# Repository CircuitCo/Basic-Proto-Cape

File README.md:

Basic-Proto-Cape
================
The Basic Proto Cape is designed to break out 26 signals from the expansion headers of the BeagleBone Black including GPIO, I2C, SPI, UART, PWM, analog inputs, +5V, +3V3, and +1.8V (analog). These signals can be accessed via a 26-pin male header.

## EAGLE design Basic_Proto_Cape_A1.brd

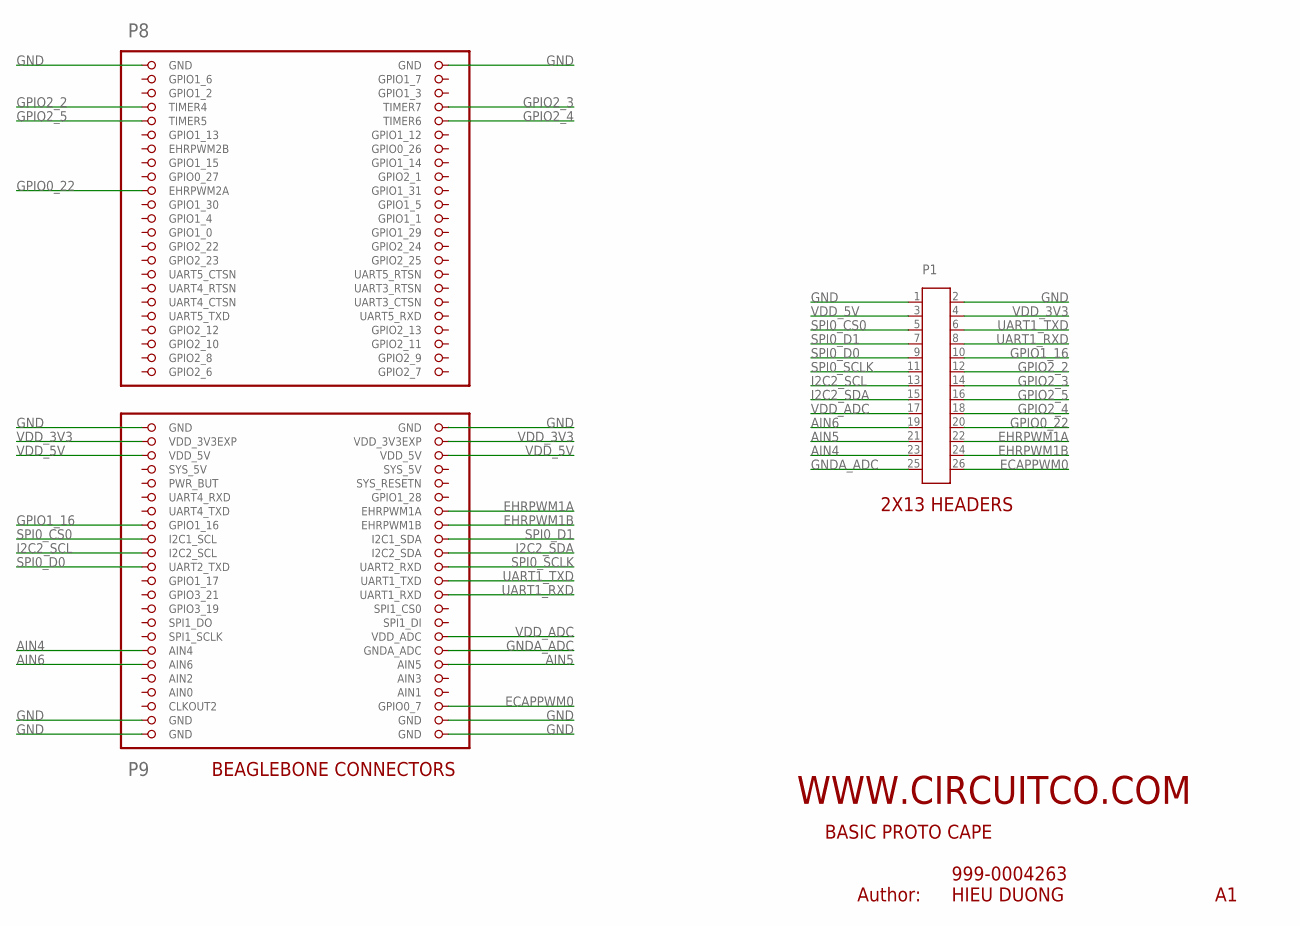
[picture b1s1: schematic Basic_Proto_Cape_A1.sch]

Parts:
P1: HEADER2X13TH; 2X13-TH
U1: BB_OL_GENPROTO

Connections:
AIN0: U1.85 (AIN0)
AIN4: P1.23, U1.79 (AIN4)
AIN5: P1.21, U1.82 (AIN5)
AIN6: P1.19, U1.81 (AIN6)
ECAPPWM0: P1.26, U1.88 (GPIO0_7)
EHRPWM1A: P1.22, U1.60 (EHRPWM1A)
EHRPWM1B: P1.24, U1.62 (EHRPWM1B)
GND: P1.1, P1.2, U1.1 (GND), U1.2 (GND), U1.47 (GND), U1.48 (GND), U1.89 (GND), U1.90 (GND), U1.91 (GND), U1.92 (GND)
GNDA_ADC: P1.25, U1.80 (GNDA_ADC)
GPIO0_22: P1.20, U1.19 (EHRPWM2A)
GPIO1_16: P1.10, U1.61 (GPIO1_16)
GPIO2_2: P1.12, U1.7 (TIMER4)
GPIO2_3: P1.14, U1.8 (TIMER7)
GPIO2_4: P1.18, U1.10 (TIMER6)
GPIO2_5: P1.16, U1.9 (TIMER5)
I2C2_SCL: P1.13, U1.65 (I2C2_SCL)
I2C2_SDA: P1.15, U1.66 (I2C2_SDA)
SPI0_CS0: P1.5, U1.63 (I2C1_SCL)
SPI0_D0: P1.9, U1.67 (UART2_TXD)
SPI0_D1: P1.7, U1.64 (I2C1_SDA)
SPI0_SCLK: P1.11, U1.68 (UART2_RXD)
SYS_5V: U1.53 (SYS_5V)
UART1_RXD: P1.8, U1.72 (UART1_RXD)
UART1_TXD: P1.6, U1.70 (UART1_TXD)
VDD_3V3: P1.4, U1.49 (VDD_3V3EXP), U1.50 (VDD_3V3EXP)
VDD_5V: P1.3, U1.51 (VDD_5V), U1.52 (VDD_5V)
VDD_ADC: P1.17, U1.78 (VDD_ADC)

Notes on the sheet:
BEAGLEBONE CONNECTORS
2X13 HEADERS
Author:

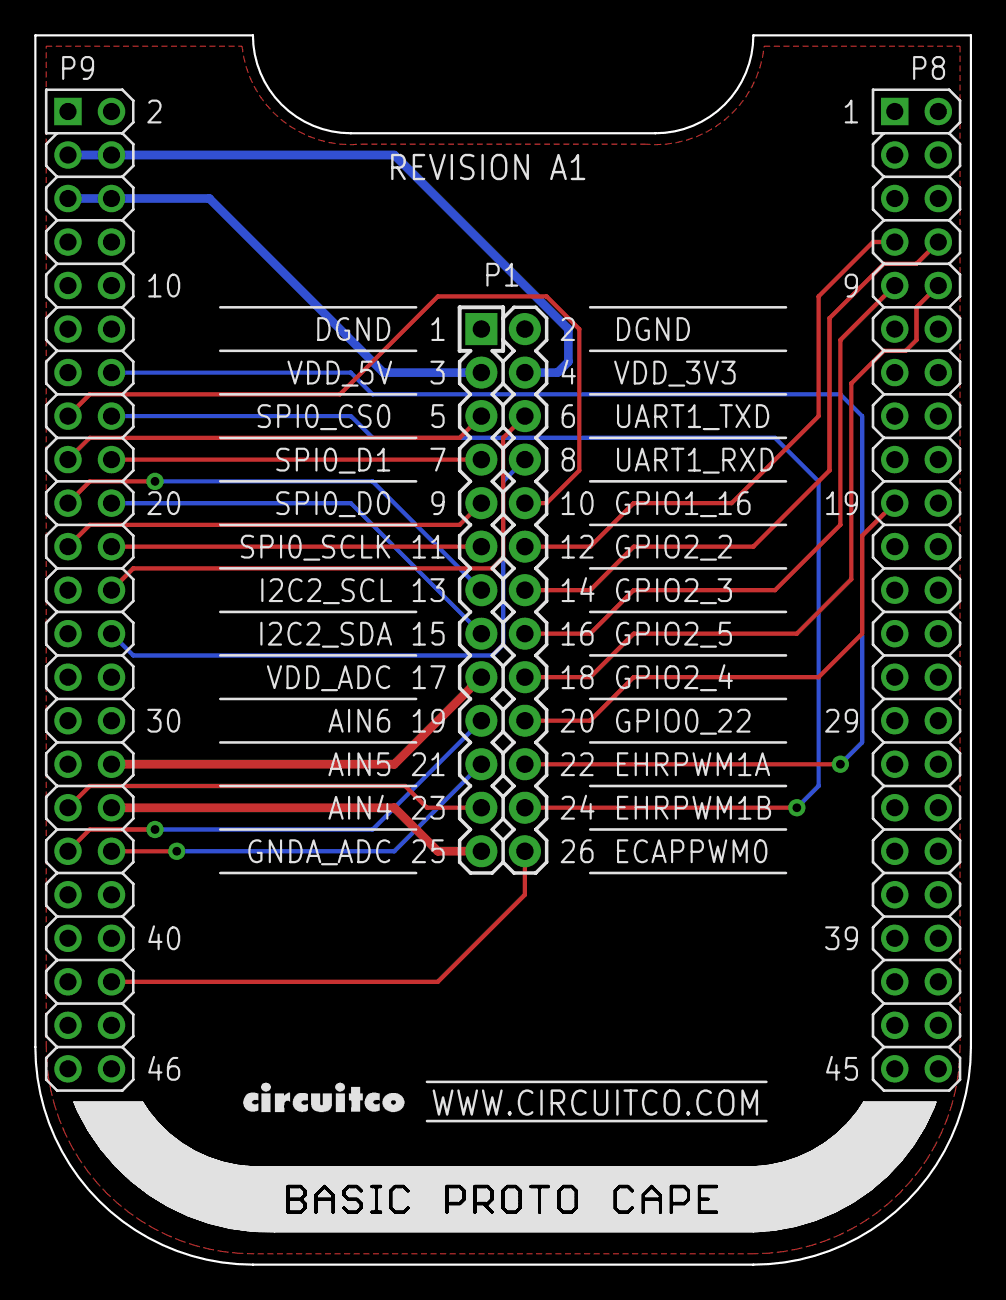
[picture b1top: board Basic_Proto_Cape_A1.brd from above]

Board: 2 copper layers, 54.6 x 71.8 mm, 5 parts (0 on the bottom side), 25 nets.

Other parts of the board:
DRILEGEND: DRILEGEND
U$1: CIRCUITCO-LOGO
U$2: NEGA-BSXPROTO-NAME

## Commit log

2014-05-28 revision a1
